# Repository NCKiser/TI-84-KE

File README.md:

# TI-84 KE
In this repo are the files and instructions associated with the TI-84 KE as discussed here:

https://www.cemetech.net/forum/viewtopic.php?p=289588

## Parts Included:
* PCB
* 52x Keycaps
* Stainless Steel Plate
* 3D Printed Case
* 3D Printed Bezel
* 10x M3 Bolts
* 2x Ribbon Cable Extenders
* Ribbon Cable Wire
* 4x Rubber Feet

## You Will Need:
* Sacrificial TI-84 CE (Instructions written based on Rev.N, non-Python)
* 52x MX-compatible keyswitches of your choice
* Soldering Iron and Solder
* Isopropal Alcohol & Q-tips
* T8 and T6 Torx Drivers
### Optional:
* Hot Glue
* Razor/Knife
* Patience

## Assembly Instructions:

### Before assembling, please install a switch testing program onto the calculator. There are BASIC and C/ASM switch tester programs provided in this repo. You can also just make a program that prints out getKey values in BASIC.

#### Start off by disassembling you TI-84 CE:

Unscrew the battery cover and remove the battery. place the battery and battery cover to the side for future use.\
Unscrew the 6 screws around the rear poerimeter of the calculator. Do not lose these screws. Keeps these screws for later use. On some models, there will also be screws under the battery, remove these as well.\
At this point, there should be no screw visible from the outside.\
Using an old hotel keycard or other thin plastic shim, pry the front and back halves of the calculator apart. Start from the bottom and work your way around the left (ON and Y= side), around the top of the screen, and then down towards the USB port on the right side. Angling your shim towards the front of the calculator may help.\
There will be a series of loud pops as you run your shim around the calculator. This is normal.\
Take care not to dig too deep with the shim, as you risk damaging the motherboard or screen.\
If the EMI shielding is able to be removed at this time, remove it.\
Using your fingernail or other small (not sharp) tool, release the ZIF connector that is retaining the screen's ribbon cable.\
Remove the 4 plastic rivets that are holding the motherboard in place. You can do this by putting a knifepoint or Philips head screwdriver in the middle of the rivet and twisting while applying moderate pressure.\
If the EMI shielding is still in place, it should be removable now.\
Remove the motherboard and screen from the front case. The buttons and keypad membrane will be loose in the front case, be careful not to make too big of a mess.\
Using moderate pressure from the inside, push the clear screen cover out from the front case. There is adhesive holding this cover in place, but consistent pressure should release it slowly.

### Disassembly Checklist

#### After dissasembly, you should be left with these parts:
* Battery
* Battery Cover
* Motherboard
* Screen
* Screen Cover
* 6x T6 screws

### Switchplate Assembly

#### Next, Assemble the switch/PCB/plate stack:

Unscrew the steel plate from the base. Use a T5 driver to remove the 10 M3 bolts. Do not loose these bolts. Inside you will find the PCB.\
If the switches you chose support LEDs from the bottom, and you want LEDs, solder the LEDs onto the PCB now, making sure of the orientation (long leg of the LED goes to the '+' sign on the PCB).\
Take 6 of your keyswitches and snap them into the steel plate at the locations pictured below (At all the "corner" locations). The pins on the bottom of the switches should be facing towards the bottom (long) edge of the plate.\

Line the PCB up with the switch pins. If your switches are PCB-mount (5-pin), press the switches into the PCB until they sit flush. This may take more force than you expect. The pins of the switches should line up with the soplderable holes on the PCB.\
With the plate/PCB/switch assemble laying face-down, ensure that the PCB is pushed or laying flush against the bottom of the switches. If you have LEDs installed, make sure they are aligned correctly.\
Solder these first 6 switches into place.\
Turning the PCB bakc face-up, insert the rest of the switches into place. Ensure that the pins on the switches are straight before attempting to put them in. There will be a distinct snap when the switch locks into the plate. If you have 5-pin switches, you may need to apply pressure from the PCB and squeeze the switch into place. Ensure that the switch bottoms are flush with the PCB, and that no switch sticks up highter than others.\
Solder the rest of the switches in place. There are 2 solderpoints per switch. If you notice one of the switch pins got bent while inserting, you can remove the switch before soldering, straighten the pins, and insert again.\
If your switches support LEDs from the top, and you want LEDs, push the LED legs through the switches and solder them now. Ensure they are and flush and "pushed down" as possible while soldering, as to avoid them interefering with the keycaps.

#### After this, you should have a complete plate/PCB/switch assembly, with LEDs optionally installed.

### Soldering All the Wires

#### Now we will combine the base, PCB, and motherboard:

Lay the switchplate facedown at the bottom of the base, oriented as if you took the top off the base and "unfolded" the switchplate from the top.\
With the motherboard component-side-up, solder the reset switch wires from the base to the motherboard< one wire nto the testpoint near the reset switch< and one wire to ground (there is a ground testpoint near the bottom).\
If you are usign LEDs, solder a wire from the battery testpoint to the PCB, and 5 wires from the PCB to the blue daughterboard that is located in the base, as pictured below:\

Insert the ribbon cable extension into the ZIF connector on the motherboard.\
Flipping the motherboard so the keypad contacts are facing up, line the USB port with the hole in the back of the case. The reset switch wires should fold and tuck under the motherboard without crossing into the battery area.\
Use 4 of the T6 screws from the calculator's case to screw the motherboard into the plastic standoffs in the bottom of the base.\
At this point, the motherboard should be screwed onto the base (keypad-side-up), the USB port should be lined up with the hole in the case, the screen extension cable should be connectd to the motherboard and laying across the base, and the reset switch wires should be soldered top the bottom of the motherboard.\
Solder 2 wires fron ON1 and ON2 on the PCB to the two on-button testpionts that aren't ground.\
If using LEDs, solder a wire from Ground on the PCB to the testpoint near the on-button that is ground.\

Solder wires from the PCB at points labebled A-H to the motherboard as pictured below, according to the wiring diagram below.\

Solder wires from the points labeled 1-7 to the motherboard as pictured below as well.\

### Testing Functionality

#### At this point, the keyboard should be functioning. Let's test it now:

Lift the base and slot the battery into place from the bottom, ensuring it is making good electrical contact.\
Gingerly connect the screen to the end of the ribbon cable extension\
If you are using LEDs, press the 4th switch from the left onm the bottom row. This should toggle the LEDs on and off.\
Press the switch 3rd from the left on the bottom row. This should turn the calculator on.\
If your calculator turns on but is unresponsive, then there probably is a short across a keypad contact, caused a key to be "pressed" constantly. Check all pads on the motherboard and switches/wires on the PCB for shorts.\

Launch your switch tester program and make sure that all of the switches work and are recognized by the calculator.\
If certain groups of switches are not responsive, check the wiring and soldering of the wires going from the PCB to the motherboard. There cold be a disconnect or a short.\
Test the reset buttom to make sure the calculator resets its ram.

#### Once all the switches work as intended, turn off the calculator and remove the battery, and unplug the screen from the ribbon cable extender.

### Final Assembly:

While folding all of the wiring neatly, lay the switchplate assembly on top of the base. The steel plate should lay flush against the top of the base without needing to apply too much pressure. Rearrange the wiring until that happens.\
Secure the swtichplate to the base by screwing in the 10 M3 bolts. To not overtighten, as you risk stripping the plastic that the base is made of. If you do strip the plastic, you can purchase M3 threaded inserts, drill the hole a little larger, and melt the inserts into place in the base.\
Fish the ribbon cable extension out form the case through the opening for the screen. Connect the screen to the ribbon cable extendor's ZIF connector.
Place the screen into the back of the 3D printed screen bezel. Using the plastic pieces provided, clip the screen into place. You may want to secure the plastic clips with a bit of hotglue. See this picture for reference:\

Being careful with the way that the ribbon cable folds/lays, snap the screen bezel into the steel place. Start by slotting the bezel into the bottom edge of the hole, then pressing down firmly around the edges. The flange around the bezel should sit flush with the steel plate.\

Use a small strip of double-sided tape, hotglue, or whatever you want, to adhere the screen cove that you salvaged from your CE into the recess on the front of the bezel.\
Turning the KE over, insert the battery and put into place the battery cover. It should be a tight fit for the battery cover. Using a medium pressure, screw the battery cover into the back of the base, making sure to not overtighten or strip the plastic.\
If desired, adhere the rubber feet into the 4 corners on the bottom.

## Now, flip it over, put on the keycaps, turn it on, and enjoy your TI-84 KE!

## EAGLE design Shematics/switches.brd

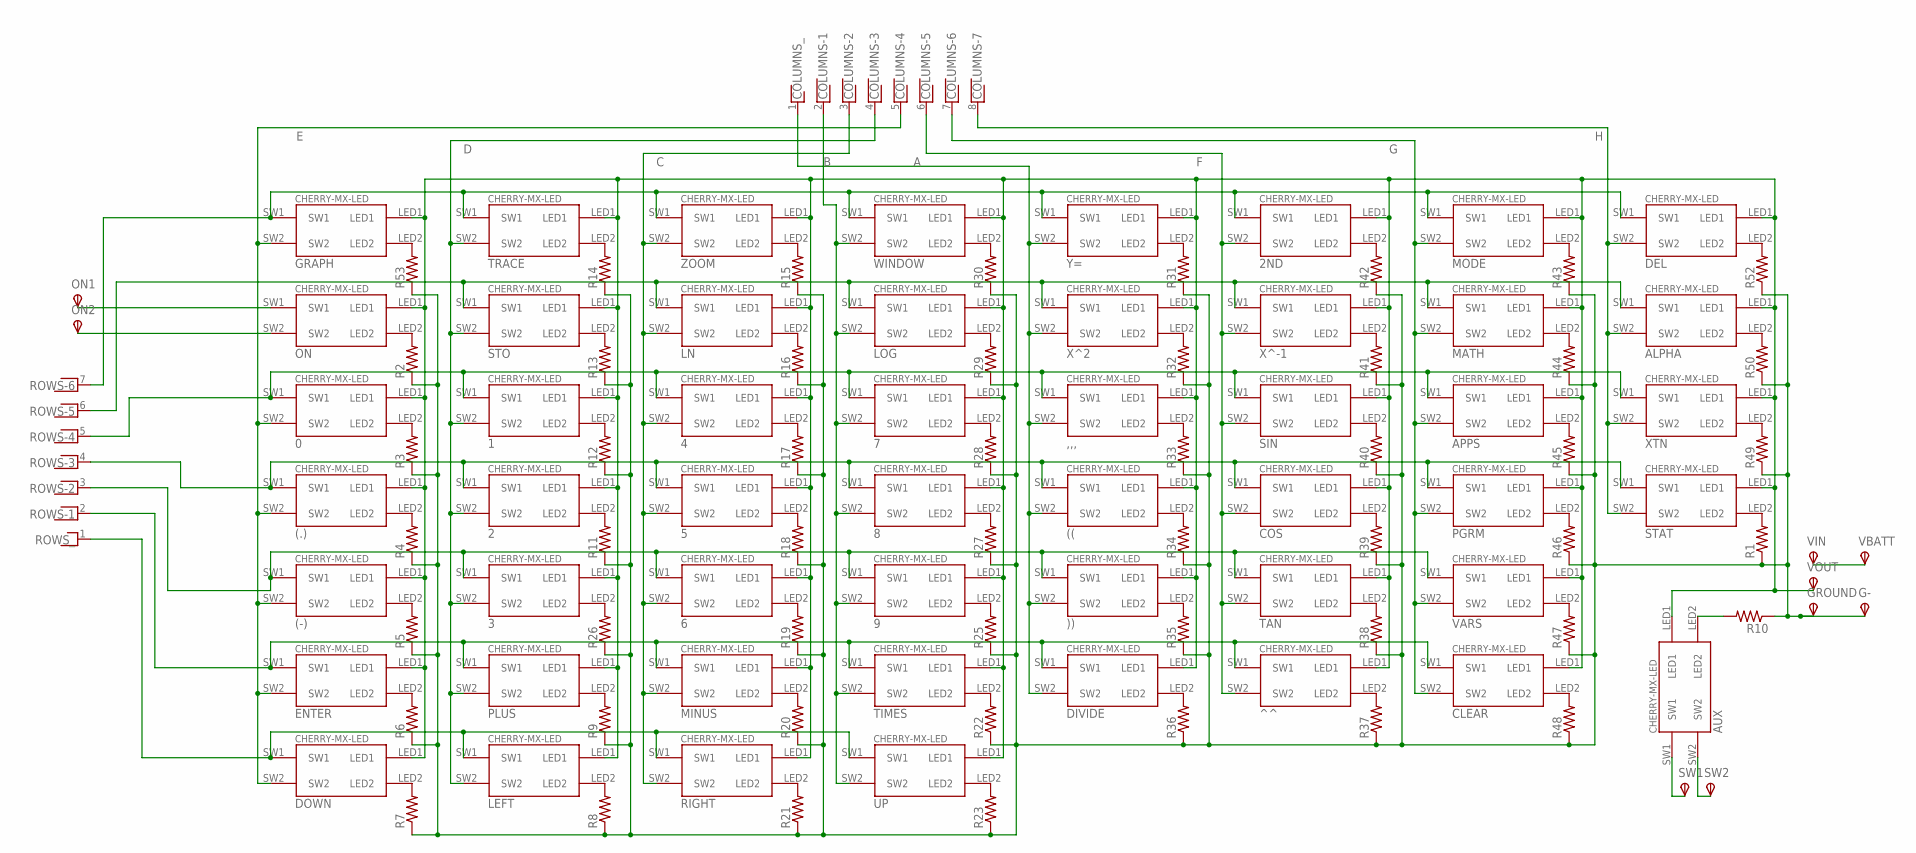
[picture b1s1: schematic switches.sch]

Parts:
0, 1, 2, 2ND, 3, 4, 5, 6, 7, 8, 9: CHERRY-MX-LEDNOSILK; CHERRY-MX-LED-NOSILK
((: CHERRY-MX-LEDNOSILK; CHERRY-MX-LED-NOSILK
(-): CHERRY-MX-LEDNOSILK; CHERRY-MX-LED-NOSILK
(.): CHERRY-MX-LEDNOSILK; CHERRY-MX-LED-NOSILK
)): CHERRY-MX-LEDNOSILK; CHERRY-MX-LED-NOSILK
,,,: CHERRY-MX-LEDNOSILK; CHERRY-MX-LED-NOSILK
ALPHA: CHERRY-MX-LEDNOSILK; CHERRY-MX-LED-NOSILK
APPS: CHERRY-MX-LEDNOSILK; CHERRY-MX-LED-NOSILK
AUX: CHERRY-MX-LEDNOSILK; CHERRY-MX-LED-NOSILK
CLEAR: CHERRY-MX-LEDNOSILK; CHERRY-MX-LED-NOSILK
COLUMNS: RNX7; RN-8
COS: CHERRY-MX-LEDNOSILK; CHERRY-MX-LED-NOSILK
DEL: CHERRY-MX-LEDNOSILK; CHERRY-MX-LED-NOSILK
DIVIDE: CHERRY-MX-LEDNOSILK; CHERRY-MX-LED-NOSILK
DOWN: CHERRY-MX-LEDNOSILK; CHERRY-MX-LED-NOSILK
ENTER: CHERRY-MX-LEDNOSILK; CHERRY-MX-LED-NOSILK
G-: TPSPAD1-17; P1-17
GRAPH: CHERRY-MX-LEDNOSILK; CHERRY-MX-LED-NOSILK
GROUND: TPSPAD1-17; P1-17
LEFT: CHERRY-MX-LEDNOSILK; CHERRY-MX-LED-NOSILK
LN: CHERRY-MX-LEDNOSILK; CHERRY-MX-LED-NOSILK
LOG: CHERRY-MX-LEDNOSILK; CHERRY-MX-LED-NOSILK
MATH: CHERRY-MX-LEDNOSILK; CHERRY-MX-LED-NOSILK
MINUS: CHERRY-MX-LEDNOSILK; CHERRY-MX-LED-NOSILK
MODE: CHERRY-MX-LEDNOSILK; CHERRY-MX-LED-NOSILK
ON: CHERRY-MX-LEDNOSILK; CHERRY-MX-LED-NOSILK
ON1, ON2: TPSPAD1-17; P1-17
PGRM: CHERRY-MX-LEDNOSILK; CHERRY-MX-LED-NOSILK
PLUS: CHERRY-MX-LEDNOSILK; CHERRY-MX-LED-NOSILK
R1, R2, R3, R4, R5, R6, R7, R8, R9, R10, R11, R12, R13, R14, R15, R16, R17, R18, R19, R20, R21, R22, R23, R25, R26, R27, R28, R29, R30, R31, R32, R33, R34, R35, R36, R37, R38, R39, R40, R41, R42, R43, R44, R45, R46, R47, R48, R49, R50, R52, R53: R-US_R0805; R0805
RIGHT: CHERRY-MX-LEDNOSILK; CHERRY-MX-LED-NOSILK
ROWS: RNX6; RN-7
SIN: CHERRY-MX-LEDNOSILK; CHERRY-MX-LED-NOSILK
STAT: CHERRY-MX-LEDNOSILK; CHERRY-MX-LED-NOSILK
STO: CHERRY-MX-LEDNOSILK; CHERRY-MX-LED-NOSILK
SW1, SW2: TPSPAD1-17; P1-17
TAN: CHERRY-MX-LEDNOSILK; CHERRY-MX-LED-NOSILK
TIMES: CHERRY-MX-LEDNOSILK; CHERRY-MX-LED-NOSILK
TRACE: CHERRY-MX-LEDNOSILK; CHERRY-MX-LED-NOSILK
UP: CHERRY-MX-LEDNOSILK; CHERRY-MX-LED-NOSILK
VARS: CHERRY-MX-LEDNOSILK; CHERRY-MX-LED-NOSILK
VBATT: TPSPAD1-17; P1-17
VIN: TPSPAD1-17; P1-17
VOUT: TPSPAD1-17; P1-17
WINDOW: CHERRY-MX-LEDNOSILK; CHERRY-MX-LED-NOSILK
XTN: CHERRY-MX-LEDNOSILK; CHERRY-MX-LED-NOSILK
X^2: CHERRY-MX-LEDNOSILK; CHERRY-MX-LED-NOSILK
X^-1: CHERRY-MX-LEDNOSILK; CHERRY-MX-LED-NOSILK
Y=: CHERRY-MX-LEDNOSILK; CHERRY-MX-LED-NOSILK
ZOOM: CHERRY-MX-LEDNOSILK; CHERRY-MX-LED-NOSILK
^^: CHERRY-MX-LEDNOSILK; CHERRY-MX-LED-NOSILK

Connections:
A: ((.SW2, )).SW2, ,,,.SW2, COLUMNS.1, DIVIDE.SW2, X^2.SW2, Y=.SW2
B: 7.SW2, 8.SW2, 9.SW2, COLUMNS.2, LOG.SW2, TIMES.SW2, UP.SW2, WINDOW.SW2
C: 4.SW2, 5.SW2, 6.SW2, COLUMNS.3, LN.SW2, MINUS.SW2, RIGHT.SW2, ZOOM.SW2
D: 1.SW2, 2.SW2, 3.SW2, COLUMNS.4, LEFT.SW2, PLUS.SW2, STO.SW2, TRACE.SW2
E: 0.SW2, (-).SW2, (.).SW2, COLUMNS.5, DOWN.SW2, ENTER.SW2, GRAPH.SW2
F: 2ND.SW2, COLUMNS.6, COS.SW2, SIN.SW2, TAN.SW2, X^-1.SW2, ^^.SW2
G: APPS.SW2, CLEAR.SW2, COLUMNS.7, MATH.SW2, MODE.SW2, PGRM.SW2, VARS.SW2
H: ALPHA.SW2, COLUMNS.8, DEL.SW2, STAT.SW2, XTN.SW2
unnamed: 2ND.SW1, DEL.SW1, GRAPH.SW1, MODE.SW1, ROWS.7, TRACE.SW1, WINDOW.SW1, Y=.SW1, ZOOM.SW1
unnamed: ALPHA.SW1, LN.SW1, LOG.SW1, MATH.SW1, ROWS.6, STO.SW1, X^2.SW1, X^-1.SW1
unnamed: 0.SW1, 1.SW1, 4.SW1, 7.SW1, ,,,.SW1, APPS.SW1, ROWS.5, SIN.SW1, XTN.SW1
unnamed: 2.SW1, 5.SW1, 8.SW1, ((.SW1, (.).SW1, COS.SW1, PGRM.SW1, ROWS.4, STAT.SW1
unnamed: 3.SW1, 6.SW1, 9.SW1, (-).SW1, )).SW1, ROWS.3, TAN.SW1, VARS.SW1
unnamed: CLEAR.SW1, DIVIDE.SW1, ENTER.SW1, MINUS.SW1, PLUS.SW1, ROWS.2, TIMES.SW1, ^^.SW1
unnamed: DOWN.SW1, LEFT.SW1, RIGHT.SW1, ROWS.1, UP.SW1
unnamed: ON.LED2, R2.2
unnamed: 0.LED2, R3.2
unnamed: (.).LED2, R4.2
unnamed: (-).LED2, R5.2
unnamed: ENTER.LED2, R6.2
unnamed: DOWN.LED2, R7.2
unnamed: LEFT.LED2, R8.2
unnamed: PLUS.LED2, R9.2
unnamed: 2.LED2, R11.2
unnamed: 1.LED2, R12.2
unnamed: R13.2, STO.LED2
unnamed: R14.2, TRACE.LED2
unnamed: R15.2, ZOOM.LED2
unnamed: LN.LED2, R16.2
unnamed: 4.LED2, R17.2
unnamed: 5.LED2, R18.2
unnamed: 6.LED2, R19.2
unnamed: MINUS.LED2, R20.2
unnamed: R21.2, RIGHT.LED2
unnamed: R22.2, TIMES.LED2
unnamed: R23.2, UP.LED2
unnamed: 9.LED2, R25.2
unnamed: 3.LED2, R26.2
unnamed: 8.LED2, R27.2
unnamed: 7.LED2, R28.2
unnamed: LOG.LED2, R29.2
unnamed: R30.2, WINDOW.LED2
unnamed: R31.2, Y=.LED2
unnamed: R32.2, X^2.LED2
unnamed: ,,,.LED2, R33.2
unnamed: ((.LED2, R34.2
unnamed: )).LED2, R35.2
unnamed: DIVIDE.LED2, R36.2
unnamed: R37.2, ^^.LED2
unnamed: R38.2, TAN.LED2
unnamed: COS.LED2, R39.2
unnamed: R40.2, SIN.LED2
unnamed: R41.2, X^-1.LED2
unnamed: 2ND.LED2, R42.2
unnamed: MODE.LED2, R43.2
unnamed: MATH.LED2, R44.2
unnamed: APPS.LED2, R45.2
unnamed: PGRM.LED2, R46.2
unnamed: R47.2, VARS.LED2
unnamed: CLEAR.LED2, R48.2
unnamed: GRAPH.LED2, R53.2
unnamed: R1.2, STAT.LED2
unnamed: R49.2, XTN.LED2
unnamed: ALPHA.LED2, R50.2
unnamed: DEL.LED2, R52.2
unnamed: G-.TP, GROUND.TP, R1.1, R2.1, R3.1, R4.1, R5.1, R6.1, R7.1, R8.1, R9.1, R10.1, R11.1, R12.1, R13.1, R14.1, R15.1, R16.1, R17.1, R18.1, R19.1, R20.1, R21.1, R22.1, R23.1, R25.1, R26.1, R27.1, R28.1, R29.1, R30.1, R31.1, R32.1, R33.1, R34.1, R35.1, R36.1, R37.1, R38.1, R39.1, R40.1, R41.1, R42.1, R43.1, R44.1, R45.1, R46.1, R47.1, R48.1, R49.1, R50.1, R52.1, R53.1
unnamed: AUX.LED2, R10.2
unnamed: AUX.SW1, SW1.TP
unnamed: AUX.SW2, SW2.TP
unnamed: VBATT.TP, VIN.TP
unnamed: ON.SW1, ON1.TP
unnamed: ON.SW2, ON2.TP
unnamed: 0.LED1, 1.LED1, 2.LED1, 2ND.LED1, 3.LED1, 4.LED1, 5.LED1, 6.LED1, 7.LED1, 8.LED1, 9.LED1, ((.LED1, (-).LED1, (.).LED1, )).LED1, ,,,.LED1, ALPHA.LED1, APPS.LED1, AUX.LED1, CLEAR.LED1, COS.LED1, DEL.LED1, DIVIDE.LED1, DOWN.LED1, ENTER.LED1, GRAPH.LED1, LEFT.LED1, LN.LED1, LOG.LED1, MATH.LED1, MINUS.LED1, MODE.LED1, ON.LED1, PGRM.LED1, PLUS.LED1, RIGHT.LED1, SIN.LED1, STAT.LED1, STO.LED1, TAN.LED1, TIMES.LED1, TRACE.LED1, UP.LED1, VARS.LED1, VOUT.TP, WINDOW.LED1, XTN.LED1, X^2.LED1, X^-1.LED1, Y=.LED1, ZOOM.LED1, ^^.LED1

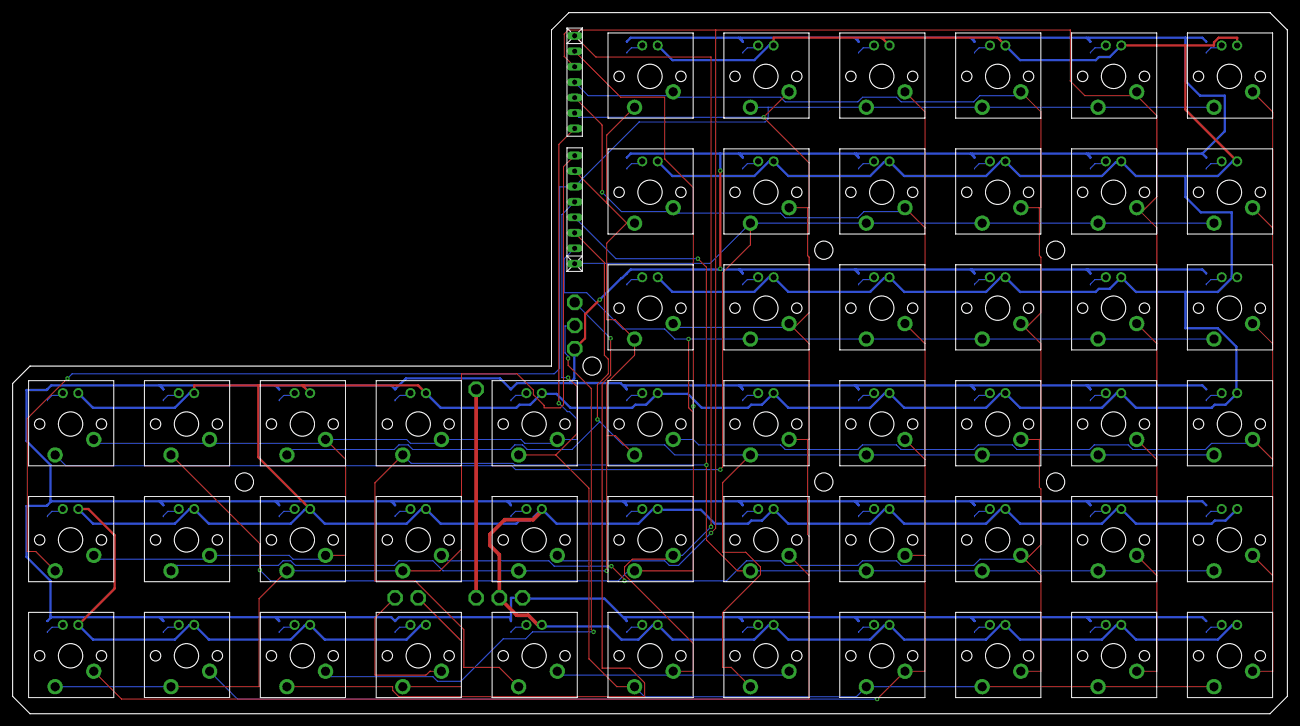
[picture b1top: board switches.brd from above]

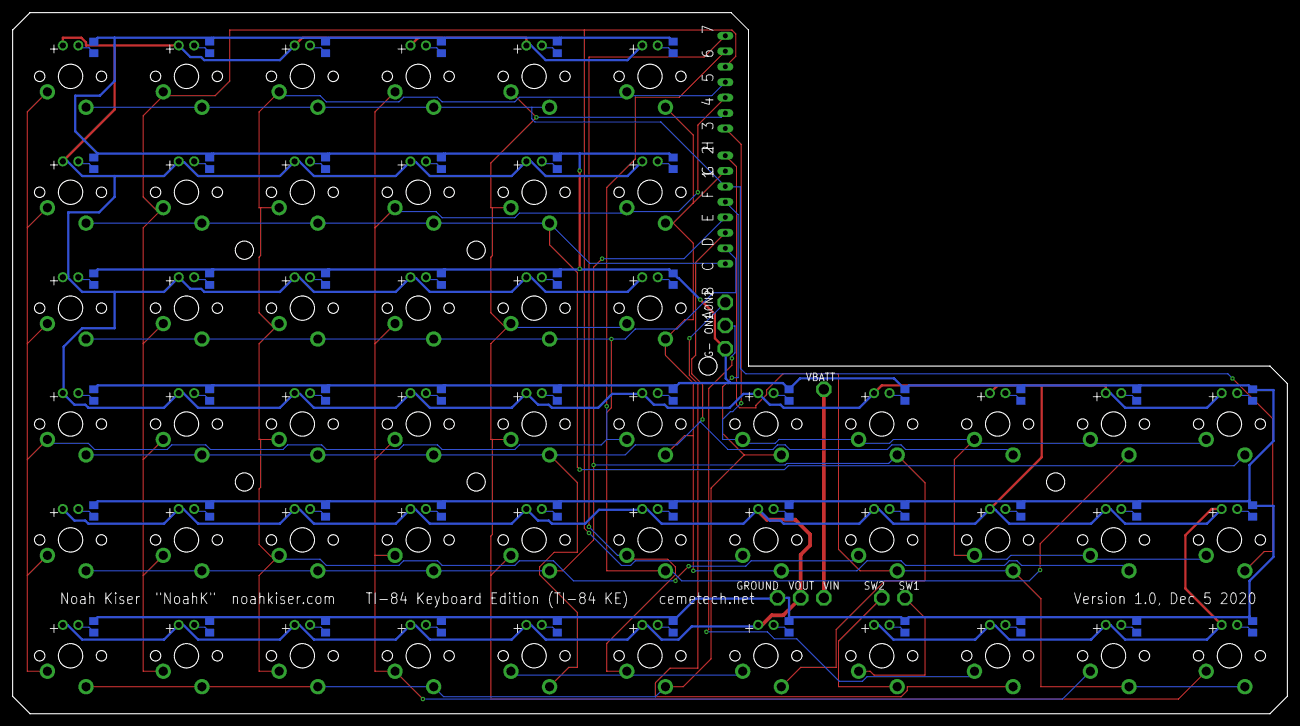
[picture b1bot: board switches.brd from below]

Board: 2 copper layers, 209.5 x 115.3 mm, 113 parts (58 on the bottom side), 73 nets.

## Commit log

2021-05-22 Create Here_are_some_pictures
2021-05-24 Create Schematics_here
2021-05-24 Rename Schematics_here to EAGLE_compatible
2022-02-27 Added plate files
